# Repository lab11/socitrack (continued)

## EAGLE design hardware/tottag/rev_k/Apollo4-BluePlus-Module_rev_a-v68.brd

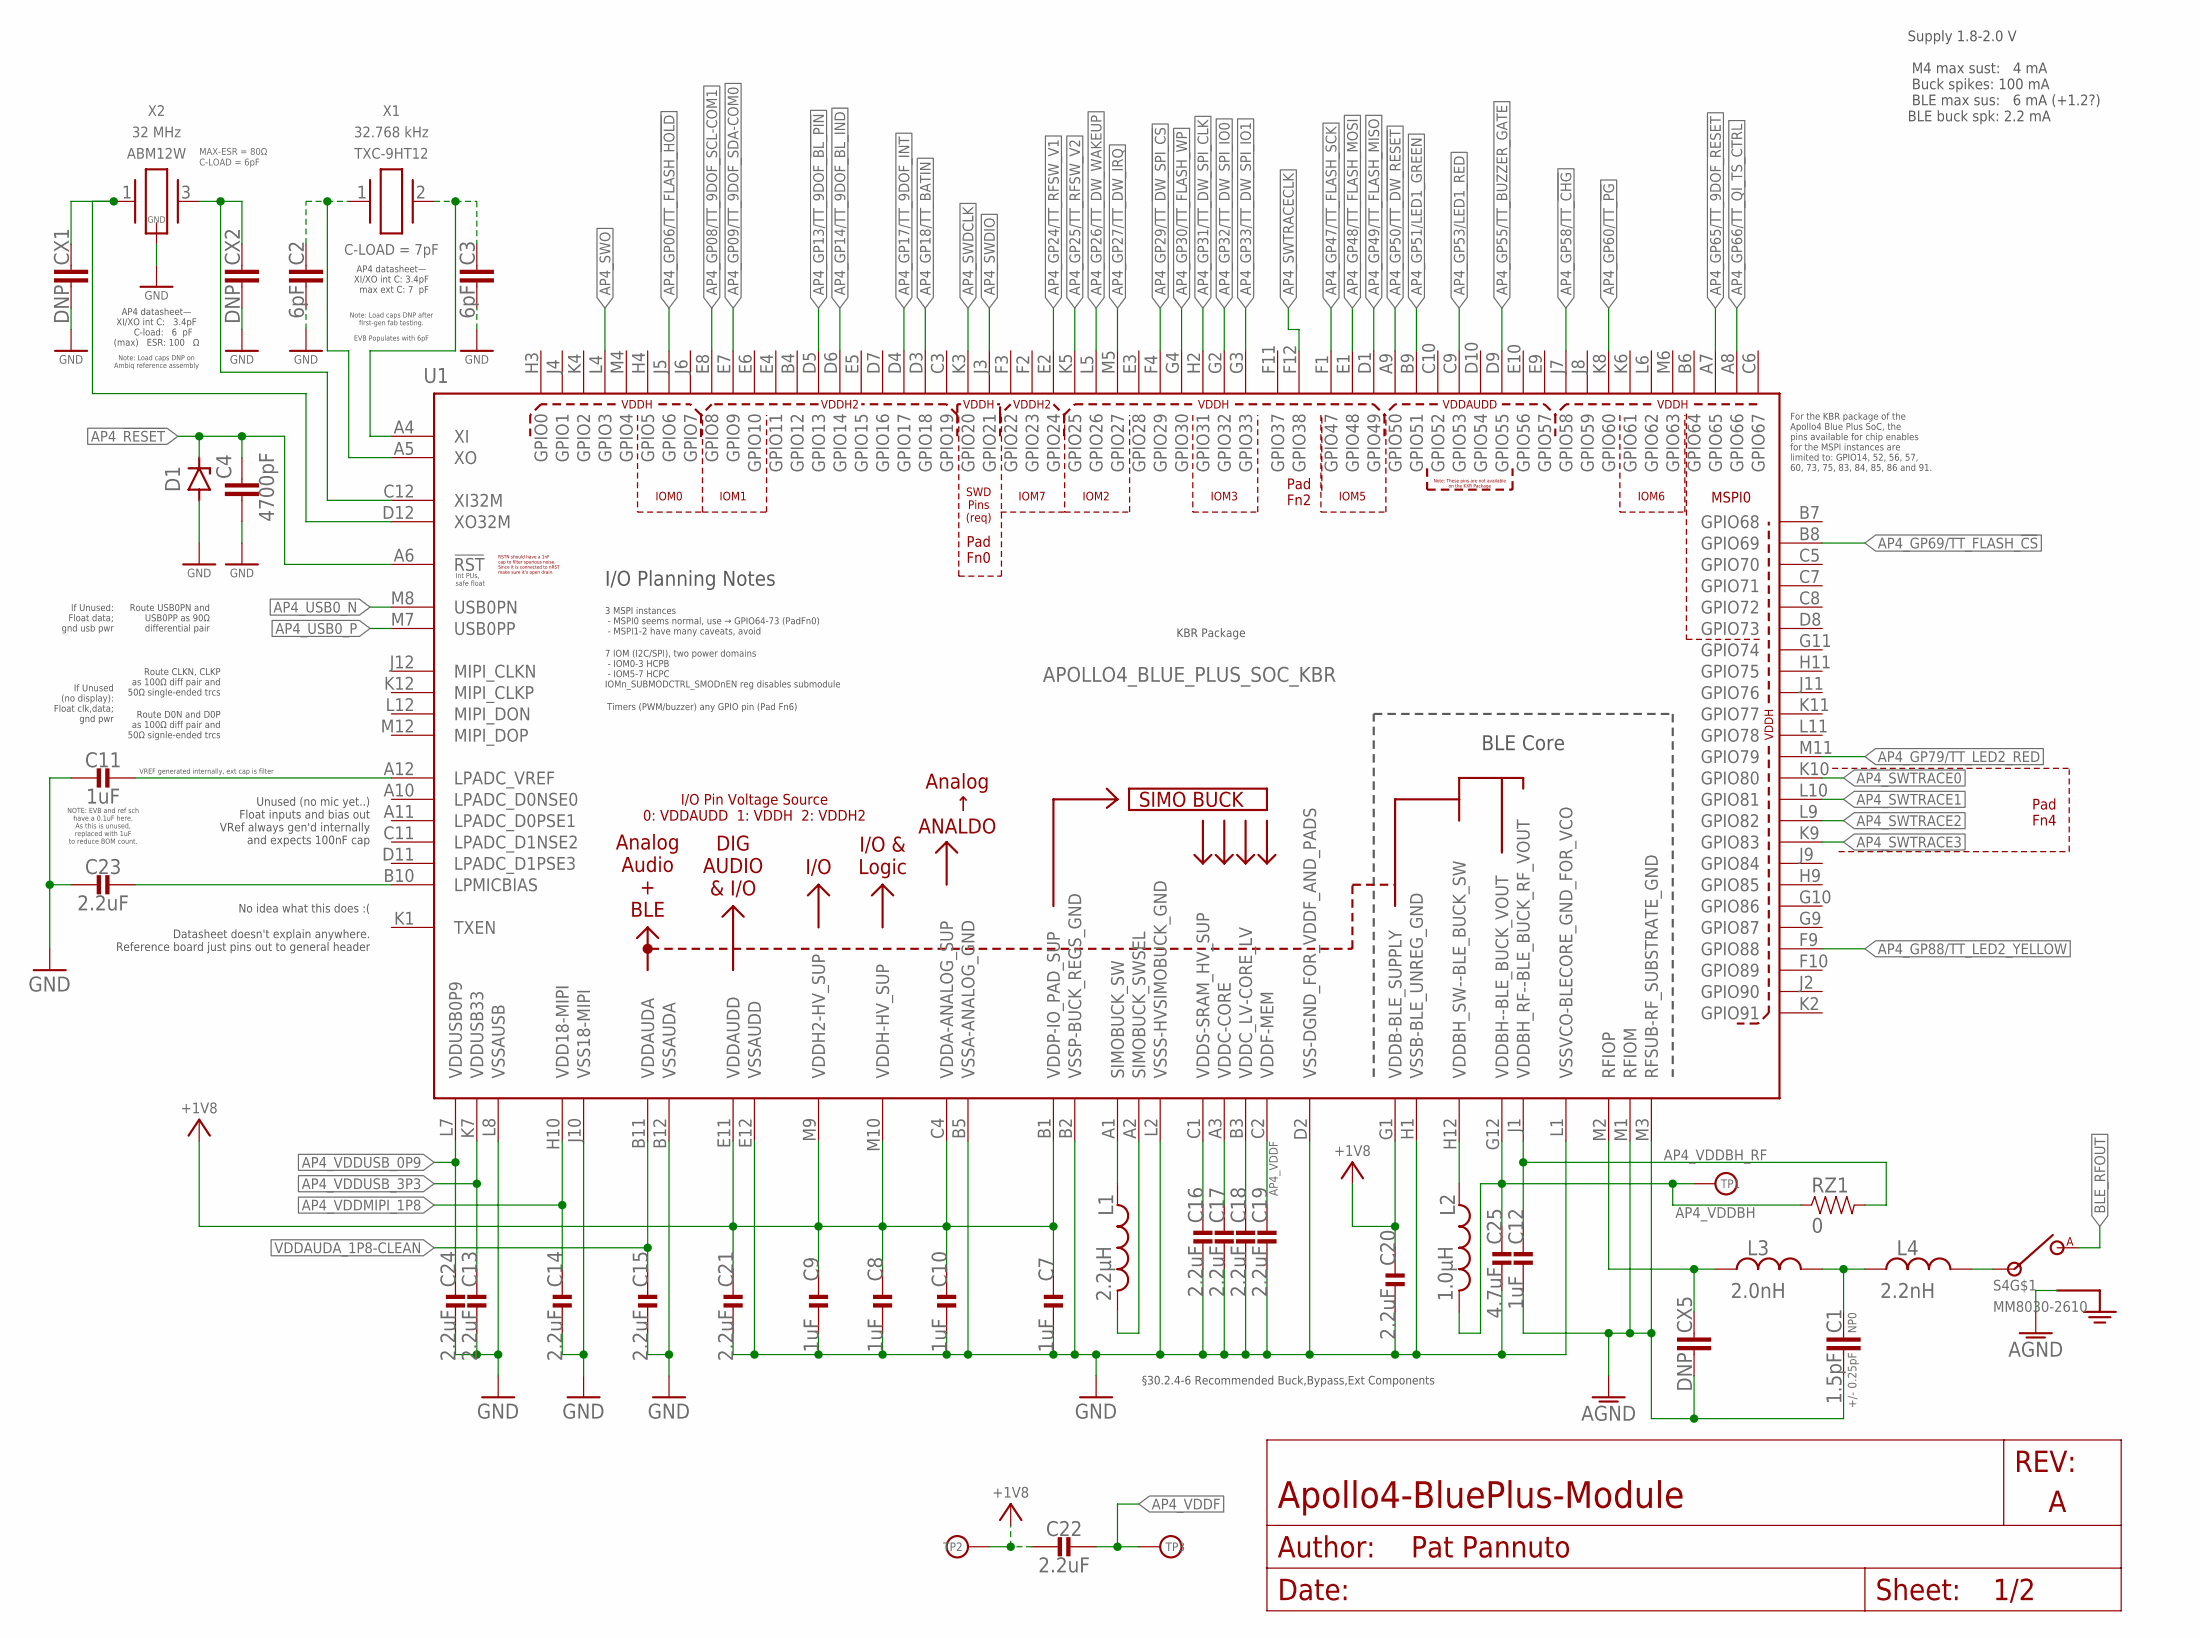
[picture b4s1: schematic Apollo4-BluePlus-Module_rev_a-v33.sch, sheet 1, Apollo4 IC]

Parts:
C1: 1.5pF; CAPC1005X60; TOLERANCE +/- 0.25pF; MPN C0402C159C5GAC7867
C2, C3: 6pF; CAPC1005X60; MPN GCM1555C1H6R0BA16D
C4: 4700pF; CAPC1005X60; MPN KGM05AR71E472KH
C7, C8, C9, C10, C11, C12: 1uF; 0201_CAP; MPN GRM033R61A105ME44D
C13, C14, C15, C16, C17, C18, C19, C20, C21, C22, C23, C24: 2.2uF; 0201_CAP; MPN GRM033R61A225KE47D
C25: 4.7uF; 0402_CAP; MPN CL05A475MP5NRNC
CX1, CX2, CX5: DNP; CAPC1005X60
D1: ZENER; SODFL1608X70; MPN PESD5V0X1UB,135
L1: 2.2µH; 0805_CAP; MPN DFE201210U-2R2M=P2
L2: 1.0µH; 0603_CAP; MPN DFE18SAN1R0ME0L
L3: 2.0nH; INDC1006X60N; TOLERANCE +/- 0.1 nH; MPN CTTF0402F-2N0B
L4: 2.2nH; INDC1006X60N; TOLERANCE +/- 0.1 nH; MPN CTTF0402F-2N2B
RZ1: 0; 0402_RES; MPN RMCF0402ZT0R00
S4: MM8030-2610
TP1: VDDBH; PAD.03X.03
TP2: VDDP; PAD.03X.03
TP3: VDDF; PAD.03X.03
U1: APOLLO4_BLUE_PLUS_SOC_KBR; APOLLO4_BLUE_SOC_BGA
X1: TXC-9HT12; MPN 9HT12-32.768KDZY-T
X2: ABM12W; MPN ABM12W-32.0000MHZ-6-D1X-T3

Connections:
+1V8: C7.P$1 (1), C8.P$1 (1), C9.P$1 (1), C10.P$1 (1), C20.P$1 (1), C21.P$1 (1), C22.P$2 (2), TP2.P$1, U1.B1 (VDDP-IO_PAD_SUP), U1.C4 (VDDA-ANALOG_SUP), U1.E11 (VDDAUDD), U1.G1 (VDDB-BLE_SUPPLY), U1.M9 (VDDH2-HV_SUP), U1.M10 (VDDH-HV_SUP); also elsewhere on the board
AGND: C1.2, C12.P$2 (2), CX5.2, S4.G1 (GND), S4.G2 (GND), U1.M1 (RFIOM), U1.M3 (RFSUB-RF_SUBSTRATE_GND); also elsewhere on the board
AP4_!RESET: C4.1, D1.1 (C), U1.A6 (!RST); also elsewhere on the board
AP4_GP06/TT_FLASH_!HOLD: U1.J5 (GPIO6); also elsewhere on the board
AP4_GP08/TT_9DOF_SCL-COM1: U1.E8 (GPIO8); also elsewhere on the board
AP4_GP09/TT_9DOF_SDA-COM0: U1.E7 (GPIO9); also elsewhere on the board
AP4_GP13/TT_9DOF_!BL_PIN: U1.D5 (GPIO13); also elsewhere on the board
AP4_GP14/TT_9DOF_BL_IND: U1.D6 (GPIO14); also elsewhere on the board
AP4_GP17/TT_9DOF_INT: U1.D4 (GPIO17); also elsewhere on the board
AP4_GP18/TT_BATIN: U1.D3 (GPIO18); also elsewhere on the board
AP4_GP24/TT_RFSW_V1: U1.E2 (GPIO24); also elsewhere on the board
AP4_GP25/TT_RFSW_V2: U1.K5 (GPIO25); also elsewhere on the board
AP4_GP26/TT_DW_WAKEUP: U1.L5 (GPIO26); also elsewhere on the board
AP4_GP27/TT_DW_IRQ: U1.M5 (GPIO27); also elsewhere on the board
AP4_GP29/TT_!DW_SPI_CS: U1.F4 (GPIO29); also elsewhere on the board
AP4_GP30/TT_FLASH_!WP: U1.G4 (GPIO30); also elsewhere on the board
AP4_GP31/TT_DW_SPI_CLK: U1.H2 (GPIO31); also elsewhere on the board
AP4_GP32/TT_DW_SPI_IO0: U1.G2 (GPIO32); also elsewhere on the board
AP4_GP33/TT_DW_SPI_IO1: U1.G3 (GPIO33); also elsewhere on the board
AP4_GP47/TT_FLASH_SCK: U1.F1 (GPIO47); also elsewhere on the board
AP4_GP48/TT_FLASH_MOSI: U1.E1 (GPIO48); also elsewhere on the board
AP4_GP49/TT_FLASH_MISO: U1.D1 (GPIO49); also elsewhere on the board
AP4_GP50/TT_!DW_RESET: U1.A9 (GPIO50); also elsewhere on the board
AP4_GP51/LED1_GREEN: U1.B9 (GPIO51); also elsewhere on the board
AP4_GP53/LED1_RED: U1.C9 (GPIO53); also elsewhere on the board
AP4_GP55/TT_BUZZER_GATE: U1.D9 (GPIO55); also elsewhere on the board
AP4_GP58/TT_!CHG: U1.J7 (GPIO58); also elsewhere on the board
AP4_GP60/TT_!PG: U1.K8 (GPIO60); also elsewhere on the board
AP4_GP65/TT_9DOF_!RESET: U1.A7 (GPIO65); also elsewhere on the board
AP4_GP66/TT_QI_TS_CTRL: U1.A8 (GPIO66); also elsewhere on the board
AP4_GP69/TT_FLASH_!CS: U1.B8 (GPIO69); also elsewhere on the board
AP4_GP79/TT_LED2_RED: U1.M11 (GPIO79); also elsewhere on the board
AP4_GP88/TT_LED2_YELLOW: U1.F9 (GPIO88); also elsewhere on the board
AP4_LPADC_VREF: C11.P$2 (2), U1.A12 (LPADC_VREF)
AP4_LPMICBIAS: C23.P$2 (2), U1.B10 (LPMICBIAS)
AP4_RFIOP: CX5.1, L3.1, U1.M2 (RFIOP)
AP4_SWDCLK: U1.K3 (GPIO20); also elsewhere on the board
AP4_SWDIO: U1.J3 (GPIO21); also elsewhere on the board
AP4_SWO: U1.L4 (GPIO3); also elsewhere on the board
AP4_SWTRACE0: U1.K10 (GPIO80); also elsewhere on the board
AP4_SWTRACE1: U1.L10 (GPIO81); also elsewhere on the board
AP4_SWTRACE2: U1.L9 (GPIO82); also elsewhere on the board
AP4_SWTRACE3: U1.K9 (GPIO83); also elsewhere on the board
AP4_SWTRACECLK: U1.F12 (GPIO38); also elsewhere on the board
AP4_USB0_N: U1.M8 (USB0PN); also elsewhere on the board
AP4_USB0_P: U1.M7 (USB0PP); also elsewhere on the board
AP4_VDDBH: C25.1, L2.2, RZ1.1, TP1.P$1, U1.G12 (VDDBH--BLE_BUCK_VOUT)
AP4_VDDBH_RF: C12.P$1 (1), RZ1.2, U1.J1 (VDDBH_RF--BLE_BUCK_RF_VOUT)
AP4_VDDBH_SW: L2.1, U1.H12 (VDDBH_SW--BLE_BUCK_SW)
AP4_VDDC: C17.P$1 (1), U1.A3 (VDDC-CORE)
AP4_VDDC_LV: C18.P$1 (1), U1.B3 (VDDC_LV-CORE_LV)
AP4_VDDF: C19.P$1 (1), C22.P$1 (1), TP3.P$1, U1.C2 (VDDF-MEM)
AP4_VDDMIPI_1P8: C14.P$1 (1), U1.H10 (VDD18-MIPI); also elsewhere on the board
AP4_VDDS: C16.P$1 (1), U1.C1 (VDDS-SRAM_HV_SUP)
AP4_VDDUSB_0P9: C24.P$1 (1), U1.L7 (VDDUSB0P9); also elsewhere on the board
AP4_VDDUSB_3P3: C13.P$1 (1), U1.K7 (VDDUSB33); also elsewhere on the board
AP4_XI: C3.1, U1.A4 (XI), X1.2
AP4_XI32M: CX2.1, U1.C12 (XI32M), X2.3 (2)
AP4_XO: C2.1, U1.A5 (XO), X1.1
AP4_XO32M: CX1.1, U1.D12 (XO32M), X2.1
BLE_RFOUT: S4.OUT (A); also elsewhere on the board
GND: C2.2, C3.2, C4.2, C7.P$2 (2), C8.P$2 (2), C9.P$2 (2), C10.P$2 (2), C11.P$1 (1), C13.P$2 (2), C14.P$2 (2), C15.P$2 (2), C16.P$2 (2), C17.P$2 (2), C18.P$2 (2), C19.P$2 (2), C20.P$2 (2), C21.P$2 (2), C23.P$1 (1), C24.P$2 (2), C25.2, CX1.2, CX2.2, D1.2 (A), U1.B2 (VSSP-BUCK_REGS_GND), U1.B5 (VSSA-ANALOG_GND), U1.B12 (VSSAUDA), U1.D2 (VSS-DGND_FOR_VDDF_AND_PADS), U1.E12 (VSSAUDD), U1.H1 (VSSB-BLE_UNREG_GND), U1.J10 (VSS18-MIPI), U1.L1 (VSSVCO-BLECORE_GND_FOR_VCO), U1.L2 (VSSS-HVSIMOBUCK_GND), U1.L8 (VSSAUSB), X2.2 (GND), X2.4 (GND); also elsewhere on the board
unnamed: C1.1, L3.2, L4.1
unnamed: L4.2, S4.IN
SIMOBUCK_SW: L1.P$1 (1), U1.A1 (SIMOBUCK_SW)
SIMOBUCK_SWSEL: L1.P$2 (2), U1.A2 (SIMOBUCK_SWSEL)
VDDAUDA_1P8-CLEAN: C15.P$1 (1), U1.B11 (VDDAUDA); also elsewhere on the board

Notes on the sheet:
Supply 1.8-2.0 V M4 max sust: 4 mA Buck spikes: 100 mA BLE max sus: 6 mA (+1.2?) BLE buck spk: 2.2 mA
Note: Load caps DNP on Ambiq reference assembly
Int PUs, safe float
If Unused: Float data; gnd usb pwr
If Unused (no display): Float clk,data; gnd pwr
Unused (no mic yet..) Float inputs and bias out VRef always gen'd internally and expects 100nF cap
No idea what this does :( Datasheet doesn't explain anywhere. Reference board just pins out to general header
I/O Planning Notes
3 MSPI instances - MSPI0 seems normal, use → GPIO64-73 (PadFn0) - MSPI1-2 have many caveats, avoid
7 IOM (I2C/SPI), two power domains - IOM0-3 HCPB - IOM5-7 HCPC IOMn_SUBMODCTRL_SMODnEN reg disables submodule
MSPI0
IOM0
IOM1
Timers (PWM/buzzer) any GPIO pin (Pad Fn6)
KBR Package
For the KBR package of the Apollo4 Blue Plus SoC, the pins available for chip enables for the MSPI instances are limited to: GPIO14, 52, 56, 57, 60, 73, 75, 83, 84, 85, 86 and 91.
§30.2.4-6 Recommended Buck,Bypass,Ext Components
SWD Pins (req)
VREF generated internally, ext cap is filter
IOM3
AP4 datasheet— XI/XO int C: 3.4pF max ext C: 7 pF
AP4 datasheet— XI/XO int C: 3.4pF C-load: 6 pF (max) ESR: 100 Ω
Pad Fn4
Pad Fn2
Pad Fn0
Note: Load caps DNP after first-gen fab testing. EVB Populates with 6pF
Route USB0PN and USB0PP as 90Ω differential pair
Route CLKN, CLKP as 100Ω diff pair and 50Ω single-ended trcs
Route D0N and D0P as 100Ω diff pair and 50Ω signle-ended trcs
NOTE: EVB and ref sch have a 0.1uF here. As this is unused, replaced with 1uF to reduce BOM count.
IOM2
IOM5
IOM6
IOM7

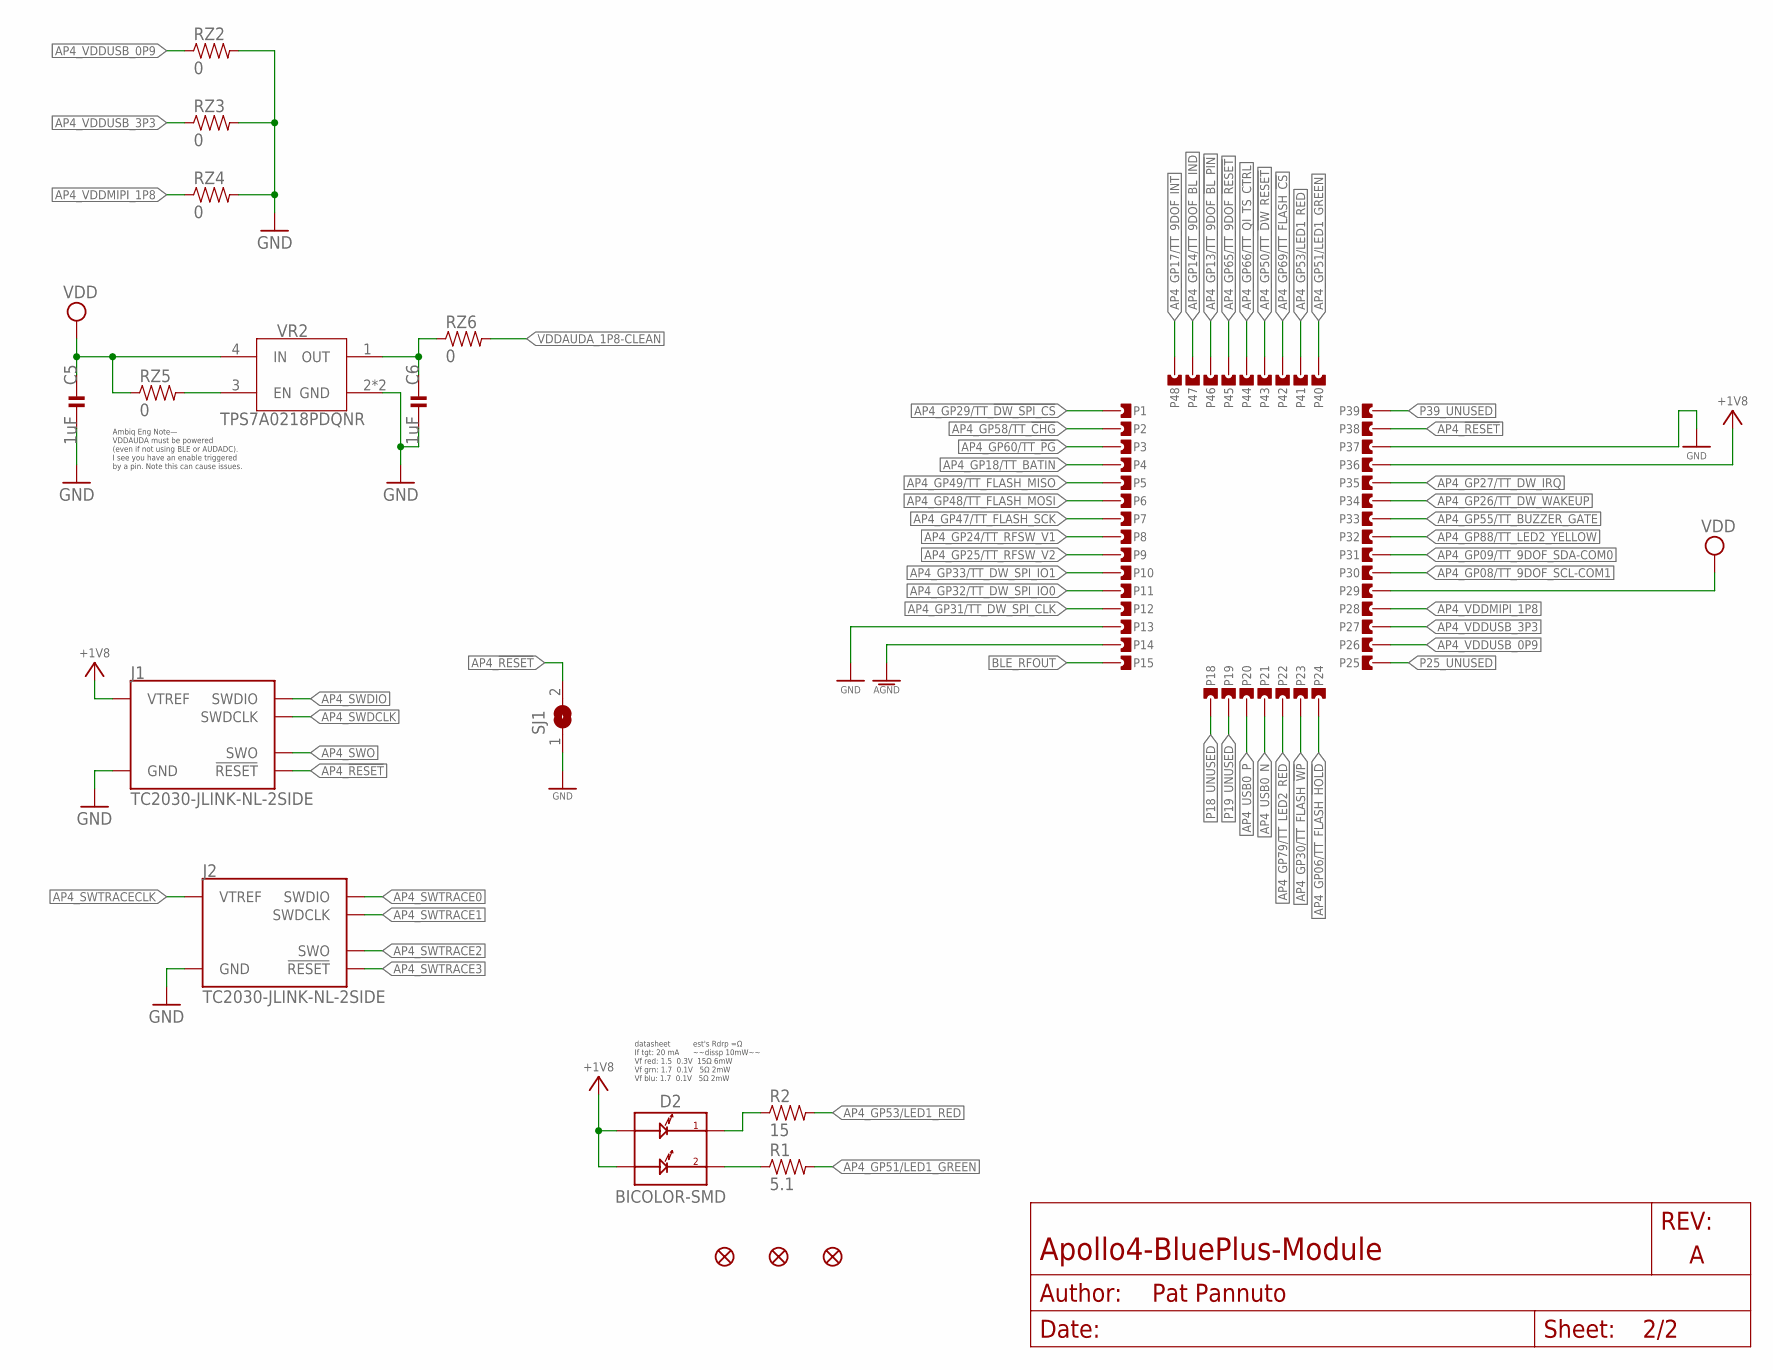
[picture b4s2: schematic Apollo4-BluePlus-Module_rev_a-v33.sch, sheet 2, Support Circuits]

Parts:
C5, C6: 1uF; 0201_CAP; MPN GRM033R61A105ME44D
D2: BICOLOR-SMD; LED-0606; MPN MCL0606FRD1GR1T
FD1, FD2, FD3: FIDUCIALUFIDUCIAL; FIDUCIAL-MICRO
J1, J2: TC2030-JLINK-NL-2SIDE; TC2030-IDC-NL-2SIDE
P1, P2, P3, P4, P5, P6, P7, P8, P9, P10, P11, P12, P13, P14, P15, P18, P19, P20, P21, P22, P23, P24, P25, P26, P27, P28, P29, P30, P31, P32, P33, P34, P35, P36, P37, P38, P39, P40, P41, P42, P43, P44, P45, P46, P47, P48: CASTELLATION4L; CASTELLATION-0.55MM_DRILL-4L
R1: 5.1; 0201_RES; MPN SR731HTTC5R10F
R2: 15; 0201_RES; MPN ERJ-1GNJ150C
RZ2, RZ3, RZ4, RZ5, RZ6: 0; 0402_RES; MPN RMCF0402ZT0R00
SJ1: SJ
VR2: TPS7A0218PDQNR; 4-XDFN-EP

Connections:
+1V8: D2.A1, D2.A2, J1.1 (VTREF), J1.B1 (VTREF), P36.P$1, P36.P$2, P36.P$3; also elsewhere on the board
AGND: P14.P$1, P14.P$2, P14.P$3; also elsewhere on the board
AP4_!RESET: J1.3 (!RESET), J1.B3 (!RESET), P38.P$1, P38.P$2, P38.P$3, SJ1.2; also elsewhere on the board
AP4_GP06/TT_FLASH_!HOLD: P24.P$1, P24.P$2, P24.P$3; also elsewhere on the board
AP4_GP08/TT_9DOF_SCL-COM1: P30.P$1, P30.P$2, P30.P$3; also elsewhere on the board
AP4_GP09/TT_9DOF_SDA-COM0: P31.P$1, P31.P$2, P31.P$3; also elsewhere on the board
AP4_GP13/TT_9DOF_!BL_PIN: P46.P$1, P46.P$2, P46.P$3; also elsewhere on the board
AP4_GP14/TT_9DOF_BL_IND: P47.P$1, P47.P$2, P47.P$3; also elsewhere on the board
AP4_GP17/TT_9DOF_INT: P48.P$1, P48.P$2, P48.P$3; also elsewhere on the board
AP4_GP18/TT_BATIN: P4.P$1, P4.P$2, P4.P$3; also elsewhere on the board
AP4_GP24/TT_RFSW_V1: P8.P$1, P8.P$2, P8.P$3; also elsewhere on the board
AP4_GP25/TT_RFSW_V2: P9.P$1, P9.P$2, P9.P$3; also elsewhere on the board
AP4_GP26/TT_DW_WAKEUP: P34.P$1, P34.P$2, P34.P$3; also elsewhere on the board
AP4_GP27/TT_DW_IRQ: P35.P$1, P35.P$2, P35.P$3; also elsewhere on the board
AP4_GP29/TT_!DW_SPI_CS: P1.P$1, P1.P$2, P1.P$3; also elsewhere on the board
AP4_GP30/TT_FLASH_!WP: P23.P$1, P23.P$2, P23.P$3; also elsewhere on the board
AP4_GP31/TT_DW_SPI_CLK: P12.P$1, P12.P$2, P12.P$3; also elsewhere on the board
AP4_GP32/TT_DW_SPI_IO0: P11.P$1, P11.P$2, P11.P$3; also elsewhere on the board
AP4_GP33/TT_DW_SPI_IO1: P10.P$1, P10.P$2, P10.P$3; also elsewhere on the board
AP4_GP47/TT_FLASH_SCK: P7.P$1, P7.P$2, P7.P$3; also elsewhere on the board
AP4_GP48/TT_FLASH_MOSI: P6.P$1, P6.P$2, P6.P$3; also elsewhere on the board
AP4_GP49/TT_FLASH_MISO: P5.P$1, P5.P$2, P5.P$3; also elsewhere on the board
AP4_GP50/TT_!DW_RESET: P43.P$1, P43.P$2, P43.P$3; also elsewhere on the board
AP4_GP51/LED1_GREEN: P40.P$1, P40.P$2, P40.P$3, R1.2; also elsewhere on the board
AP4_GP53/LED1_RED: P41.P$1, P41.P$2, P41.P$3, R2.2; also elsewhere on the board
AP4_GP55/TT_BUZZER_GATE: P33.P$1, P33.P$2, P33.P$3; also elsewhere on the board
AP4_GP58/TT_!CHG: P2.P$1, P2.P$2, P2.P$3; also elsewhere on the board
AP4_GP60/TT_!PG: P3.P$1, P3.P$2, P3.P$3; also elsewhere on the board
AP4_GP65/TT_9DOF_!RESET: P45.P$1, P45.P$2, P45.P$3; also elsewhere on the board
AP4_GP66/TT_QI_TS_CTRL: P44.P$1, P44.P$2, P44.P$3; also elsewhere on the board
AP4_GP69/TT_FLASH_!CS: P42.P$1, P42.P$2, P42.P$3; also elsewhere on the board
AP4_GP79/TT_LED2_RED: P22.P$1, P22.P$2, P22.P$3; also elsewhere on the board
AP4_GP88/TT_LED2_YELLOW: P32.P$1, P32.P$2, P32.P$3; also elsewhere on the board
AP4_LED2_BLUE_COMM: D2.C1, R2.1
AP4_LED_RED_COMM: D2.C2, R1.1
AP4_SWDCLK: J1.4 (SWDCLK), J1.B4 (SWDCLK); also elsewhere on the board
AP4_SWDIO: J1.2 (SWDIO), J1.B2 (SWDIO); also elsewhere on the board
AP4_SWO: J1.6 (SWO), J1.B6 (SWO); also elsewhere on the board
AP4_SWTRACE0: J2.2 (SWDIO), J2.B2 (SWDIO); also elsewhere on the board
AP4_SWTRACE1: J2.4 (SWDCLK), J2.B4 (SWDCLK); also elsewhere on the board
AP4_SWTRACE2: J2.6 (SWO), J2.B6 (SWO); also elsewhere on the board
AP4_SWTRACE3: J2.3 (!RESET), J2.B3 (!RESET); also elsewhere on the board
AP4_SWTRACECLK: J2.1 (VTREF), J2.B1 (VTREF); also elsewhere on the board
AP4_USB0_N: P21.P$1, P21.P$2, P21.P$3; also elsewhere on the board
AP4_USB0_P: P20.P$1, P20.P$2, P20.P$3; also elsewhere on the board
AP4_VDDMIPI_1P8: P28.P$1, P28.P$2, P28.P$3, RZ4.1; also elsewhere on the board
AP4_VDDUSB_0P9: P26.P$1, P26.P$2, P26.P$3, RZ2.1; also elsewhere on the board
AP4_VDDUSB_3P3: P27.P$1, P27.P$2, P27.P$3, RZ3.1; also elsewhere on the board
BLE_RFOUT: P15.P$1, P15.P$2, P15.P$3; also elsewhere on the board
GND: C5.P$2 (2), C6.P$2 (2), J1.5 (GND), J1.B5 (GND), J2.5 (GND), J2.B5 (GND), P13.P$1, P13.P$2, P13.P$3, P37.P$1, P37.P$2, P37.P$3, RZ2.2, RZ3.2, RZ4.2, SJ1.1, VR2.2 (GND), VR2.PAD (GND); also elsewhere on the board
P18_UNUSED: P18.P$1, P18.P$2, P18.P$3
P19_UNUSED: P19.P$1, P19.P$2, P19.P$3
P25_UNUSED: P25.P$1, P25.P$2, P25.P$3
P39_UNUSED: P39.P$1, P39.P$2, P39.P$3
VDD: C5.P$1 (1), P29.P$1, P29.P$2, P29.P$3, RZ5.1, VR2.4 (IN)
VDDAUDA_1P8-CLEAN: RZ6.2; also elsewhere on the board
VR2_EN: RZ5.2, VR2.3 (EN)
VR2_OUT: C6.P$1 (1), RZ6.1, VR2.1 (OUT)

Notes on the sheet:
Ambiq Eng Note— VDDAUDA must be powered (even if not using BLE or AUDADC). I see you have an enable triggered by a pin. Note this can cause issues.
datasheet est's Rdrp =Ω If tgt: 20 mA ~~dissp 10mW~~ Vf red: 1.5 0.3V 15Ω 6mW Vf grn: 1.7 0.1V 5Ω 2mW Vf blu: 1.7 0.1V 5Ω 2mW

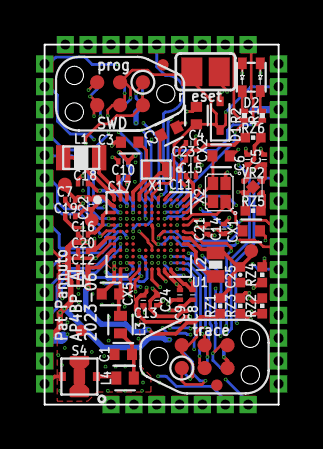
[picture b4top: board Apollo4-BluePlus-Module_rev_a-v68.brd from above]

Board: 4 copper layers, 13.0 x 20.0 mm, 102 parts (0 on the bottom side), 76 nets.

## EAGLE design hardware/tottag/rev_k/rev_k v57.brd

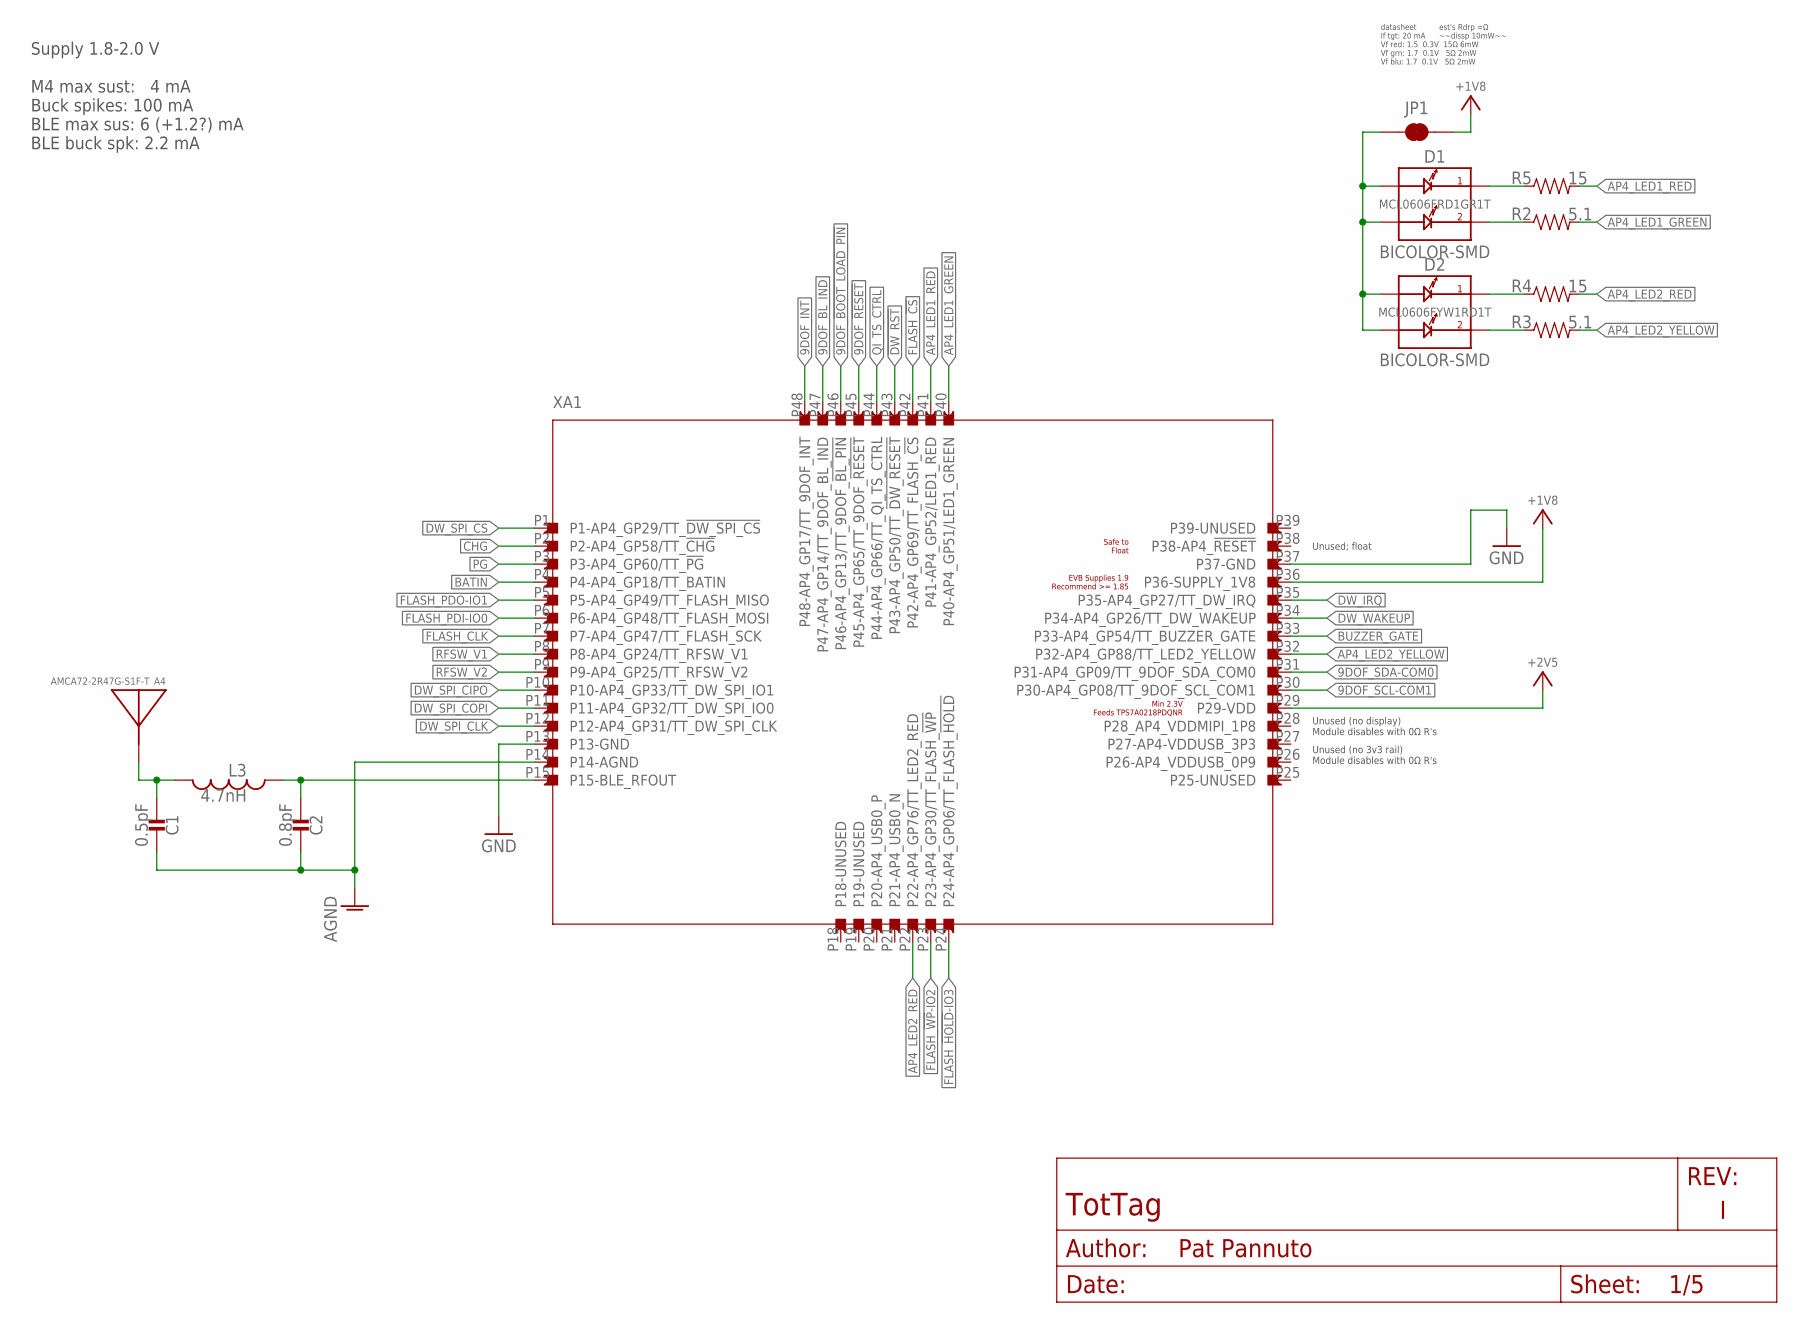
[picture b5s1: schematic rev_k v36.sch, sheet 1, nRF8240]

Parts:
A4: AMCA72-2R47G-S1F-T; AMCA72-2R470G-S1F-T
C1: 0.5pF; 0402_CAP; MPN GJM1555C1HR50WB01D
C2: 0.8pF; 0402_CAP; MPN GJM1555C1HR80WB01D
D1: BICOLOR-SMD; LED-0606; MPN MCL0606FRD1GR1T
D2: BICOLOR-SMD; LED-0606; MPN MCL0606FYW1RD1T
JP1: JUMPER-SMT_2_NC_TRACE_SILK; SMT-JUMPER_2_NC_TRACE_SILK
L3: 4.7nH; 0402_CAP; MPN LQW15AN4N7G8ZD
R2, R3: 5.1; 0402_RES; MPN RC0402JR-075R1L
R4, R5: 15; 0402_RES; MPN RC0402JR-0715RL
XA1: APOLLO4_BLUEPLUS_MODULE

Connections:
9DOF_!BOOT_LOAD_PIN: XA1.P46 (P46-AP4_GP13/TT_9DOF_!BL_PIN); also elsewhere on the board
9DOF_!RESET: XA1.P45 (P45-AP4_GP65/TT_9DOF_!RESET); also elsewhere on the board
9DOF_BL_IND: XA1.P47 (P47-AP4_GP14/TT_9DOF_BL_IND); also elsewhere on the board
9DOF_INT: XA1.P48 (P48-AP4_GP17/TT_9DOF_INT); also elsewhere on the board
9DOF_SCL-COM1: XA1.P30 (P30-AP4_GP08/TT_9DOF_SCL_COM1); also elsewhere on the board
9DOF_SDA-COM0: XA1.P31 (P31-AP4_GP09/TT_9DOF_SDA_COM0); also elsewhere on the board
!CHG: XA1.P2 (P2-AP4_GP58/TT_!CHG); also elsewhere on the board
!DW_RST: XA1.P43 (P43-AP4_GP50/TT_!DW_RESET); also elsewhere on the board
!DW_SPI_CS: XA1.P1 (P1-AP4_GP29/TT_!DW_SPI_CS); also elsewhere on the board
!PG: XA1.P3 (P3-AP4_GP60/TT_!PG); also elsewhere on the board
+1V8: JP1.2, XA1.P36 (P36-SUPPLY_1V8); also elsewhere on the board
+2V5: XA1.P29 (P29-VDD); also elsewhere on the board
AGND: C1.2, C2.2, XA1.P14 (P14-AGND)
AP4_LED1_GREEN: R2.2, XA1.P40 (P40-AP4_GP51/LED1_GREEN)
AP4_LED1_RED: R5.2, XA1.P41 (P41-AP4_GP52/LED1_RED)
AP4_LED2_BLUE_COMM: D1.C1, R5.1
AP4_LED2_RED: R4.2, XA1.P22 (P22-AP4_GP76/TT_LED2_RED)
AP4_LED2_YELLOW: R3.2, XA1.P32 (P32-AP4_GP88/TT_LED2_YELLOW)
AP4_LED_BLUE_COMM: D2.C2, R3.1
AP4_LED_GREEN_COMM: D2.C1, R4.1
AP4_LED_RED_COMM: D1.C2, R2.1
AP4_RFIOP: C2.1, L3.2, XA1.P15 (P15-BLE_RFOUT)
BATIN: XA1.P4 (P4-AP4_GP18/TT_BATIN); also elsewhere on the board
BLE_ANT_FEED: A4.S1, C1.1, L3.1
BUZZER_GATE: XA1.P33 (P33-AP4_GP54/TT_BUZZER_GATE); also elsewhere on the board
DW_IRQ: XA1.P35 (P35-AP4_GP27/TT_DW_IRQ); also elsewhere on the board
DW_SPI_CIPO: XA1.P10 (P10-AP4_GP33/TT_DW_SPI_IO1); also elsewhere on the board
DW_SPI_CLK: XA1.P12 (P12-AP4_GP31/TT_DW_SPI_CLK); also elsewhere on the board
DW_SPI_COPI: XA1.P11 (P11-AP4_GP32/TT_DW_SPI_IO0); also elsewhere on the board
DW_WAKEUP: XA1.P34 (P34-AP4_GP26/TT_DW_WAKEUP); also elsewhere on the board
FLASH_!CS: XA1.P42 (P42-AP4_GP69/TT_FLASH_!CS); also elsewhere on the board
FLASH_!HOLD!-IO3: XA1.P24 (P24-AP4_GP06/TT_FLASH_!HOLD); also elsewhere on the board
FLASH_!WP!-IO2: XA1.P23 (P23-AP4_GP30/TT_FLASH_!WP); also elsewhere on the board
FLASH_CLK: XA1.P7 (P7-AP4_GP47/TT_FLASH_SCK); also elsewhere on the board
FLASH_PDI-IO0: XA1.P6 (P6-AP4_GP48/TT_FLASH_MOSI); also elsewhere on the board
FLASH_PDO-IO1: XA1.P5 (P5-AP4_GP49/TT_FLASH_MISO); also elsewhere on the board
GND: XA1.P13 (P13-GND), XA1.P37 (P37-GND); also elsewhere on the board
LED_SUP: D1.A1, D1.A2, D2.A1, D2.A2, JP1.1
QI_TS_CTRL: XA1.P44 (P44-AP4_GP66/TT_QI_TS_CTRL); also elsewhere on the board
RFSW_V1: XA1.P8 (P8-AP4_GP24/TT_RFSW_V1); also elsewhere on the board
RFSW_V2: XA1.P9 (P9-AP4_GP25/TT_RFSW_V2); also elsewhere on the board

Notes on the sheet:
Supply 1.8-2.0 V M4 max sust: 4 mA Buck spikes: 100 mA BLE max sus: 6 (+1.2?) mA BLE buck spk: 2.2 mA
Unused (no 3v3 rail) Module disables with 0Ω R's
Unused (no display) Module disables with 0Ω R's
datasheet est's Rdrp =Ω If tgt: 20 mA ~~dissp 10mW~~ Vf red: 1.5 0.3V 15Ω 6mW Vf grn: 1.7 0.1V 5Ω 2mW Vf blu: 1.7 0.1V 5Ω 2mW
Unused; float
